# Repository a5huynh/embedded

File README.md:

embedded projects
=================

Source for various embedded projects that I've completed or in progress.

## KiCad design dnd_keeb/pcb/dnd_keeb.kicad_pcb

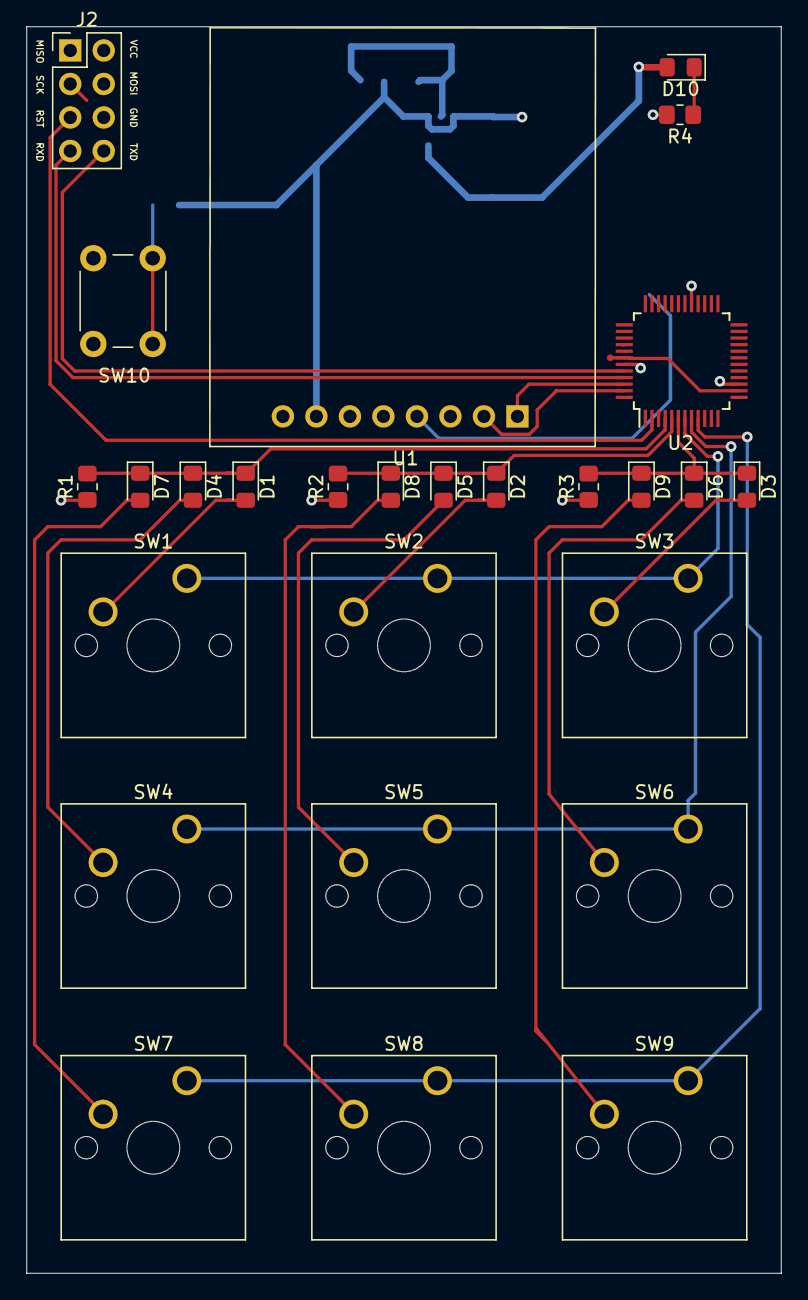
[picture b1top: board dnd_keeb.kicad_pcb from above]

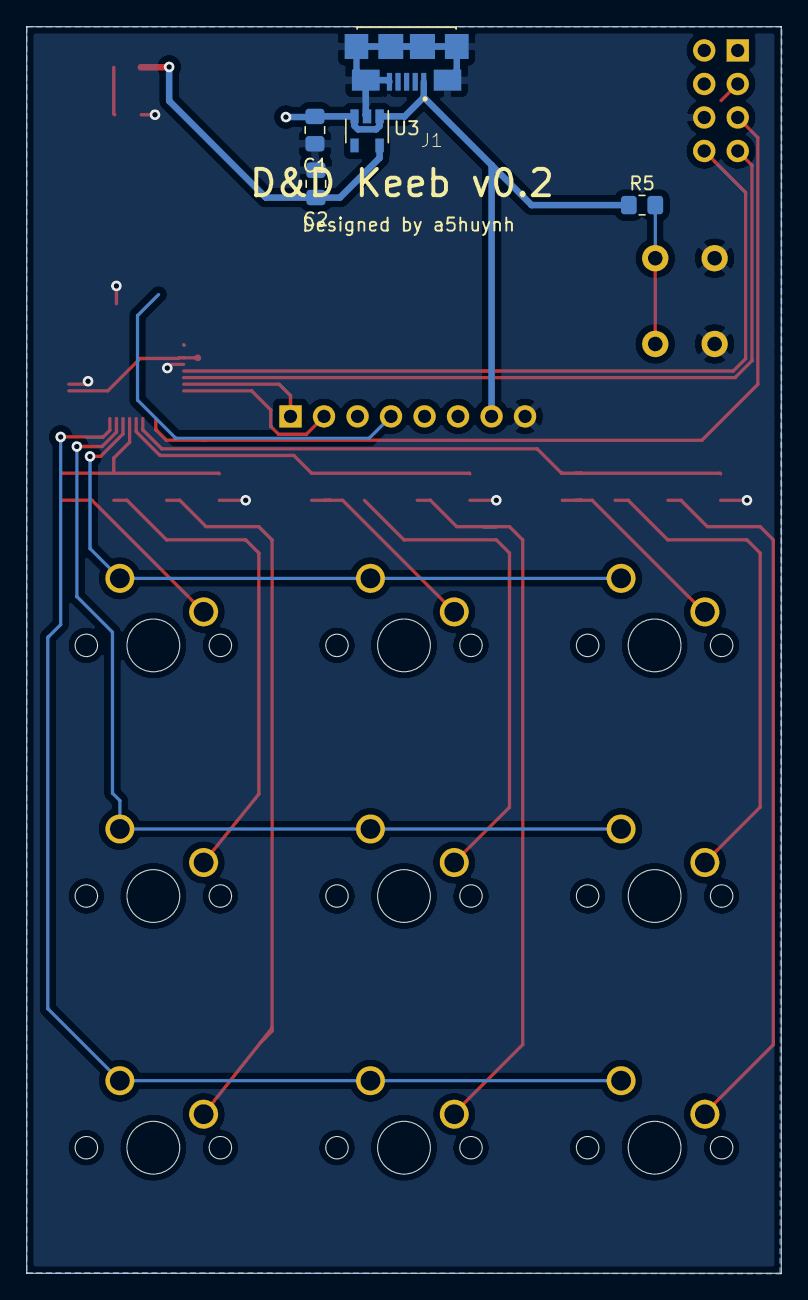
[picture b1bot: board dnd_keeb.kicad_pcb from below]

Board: 2 copper layers, 57.2 x 94.5 mm, 32 parts (5 on the bottom side), 28 nets.

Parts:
C1, C2: 1uF; C_0805_2012Metric_Pad1.18x1.45mm_HandSolder
D1, D2, D3, D4, D5, D6, D7, D8, D9: D; D_0805_2012Metric_Pad1.15x1.40mm_HandSolder
D10: PWR; LED_0805_2012Metric_Pad1.15x1.40mm_HandSolder
J1: USB-B Micro Receptacle 10118192-0002LF; AMPHENOL_10118192-0002LF
J2: Conn_02x04_Odd_Even; PinHeader_2x04_P2.54mm_Vertical
R1, R2, R3: 10k; R_0805_2012Metric_Pad1.20x1.40mm_HandSolder
R4, R5: 330; R_0805_2012Metric_Pad1.20x1.40mm_HandSolder
SW1, SW2, SW3, SW4, SW5, SW6, SW7, SW8, SW9: SW_DIP_x01; SW_Cherry_MX_1.00u_PCB
SW10: SW_Push; SW_PUSH_6mm
U1: OLED_326; Adafruit_326
U2: ATmega4809-A; TQFP-48_7x7mm_P0.5mm
U3: AP7343-33W5-7; SOT-23-5

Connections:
3v3: C2.1, D10.2, U3.5
/RXD: J2.7, U2.45
/TXD: J2.8, U2.44
COL1: SW1.1, SW2.1, SW3.1, U2.7
COL2: SW4.1, SW5.1, SW6.1, U2.8
COL3: SW7.1, SW8.1, SW9.1, U2.9
GND: C1.2, C2.2, J1.5, J1.S1, J1.S2, J1.S3, J1.S4, J1.S5, J1.S6, J2.6, R1.1, R2.1, R3.1, R4.2, SW10.1, U1.8, U2.15, U2.29, U2.43, U3.2
MISO: J2.3, U2.1
MOSI: J2.1, U2.48
unnamed: D1.2, SW1.2
unnamed: D2.2, SW2.2
unnamed: D3.2, SW3.2
unnamed: D4.2, SW4.2
unnamed: D5.2, SW5.2
unnamed: D6.2, SW6.2
unnamed: D7.2, SW7.2
unnamed: D8.2, SW8.2
unnamed: D9.2, SW9.2
unnamed: D10.1, R4.1
unnamed: R5.2, SW10.2, U2.40
ROW1: D1.1, D4.1, D7.1, R1.2, U2.4
ROW2: D2.1, D5.1, D8.1, R2.2, U2.5
ROW3: D3.1, D6.1, D9.1, R3.2, U2.6
SCK: J2.5, U2.2
SCL: U1.2, U2.47
SDA: U1.1, U2.46
UPDI: J2.4, U2.41
VCC: C1.1, J1.1, J2.2, R5.1, U1.7, U2.14, U2.42, U3.1, U3.3

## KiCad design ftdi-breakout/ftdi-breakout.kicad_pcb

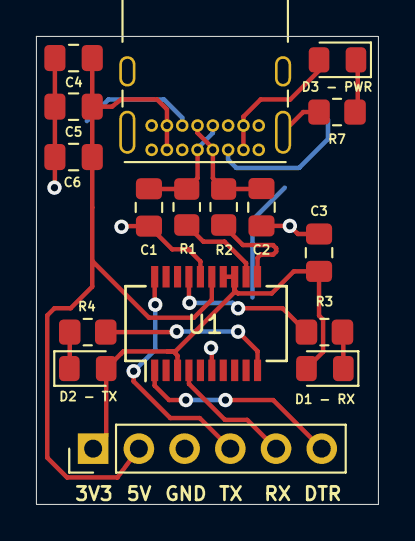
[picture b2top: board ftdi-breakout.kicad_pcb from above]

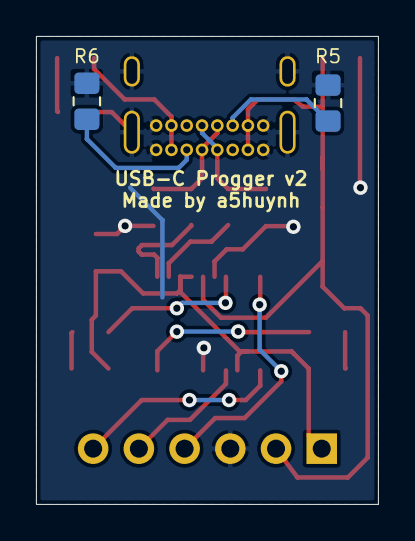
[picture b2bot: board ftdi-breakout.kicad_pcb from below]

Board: 2 copper layers, 19.0 x 26.0 mm, 19 parts (2 on the bottom side), 17 nets.

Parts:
C1, C2, C6: 47pF; C_0805_2012Metric_Pad1.18x1.45mm_HandSolder
C3, C5: 100nF; C_0805_2012Metric_Pad1.18x1.45mm_HandSolder
C4: 10nF; C_0805_2012Metric_Pad1.18x1.45mm_HandSolder
D1 - RX, D3 - PWR: RX Red; LED_0805_2012Metric_Pad1.15x1.40mm_HandSolder
D2 - TX: TX Green; LED_0805_2012Metric_Pad1.15x1.40mm_HandSolder
J1: Conn_01x06; PinHeader_1x06_P2.54mm_Vertical
J2: USB_C_Receptacle_USB2.0; USB_C_Receptacle_GCT_USB4085
R1, R2: 27; R_0805_2012Metric_Pad1.20x1.40mm_HandSolder
R3, R4, R7: 270; R_0805_2012Metric_Pad1.20x1.40mm_HandSolder
R5, R6: 5.1K; R_0805_2012Metric_Pad1.20x1.40mm_HandSolder
U1: FT231XS; SSOP-20_3.9x8.7mm_P0.635mm

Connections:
/3V3OUT: C3.2, D1 - RX.2, D2 - TX.2, J1.1, U1.3, U1.13, U1.14
/CBUS1: R3.1, U1.17
/CBUS2: R4.1, U1.10
/D+: C2.2, J2.A6, J2.B6, R2.2
/D-: C1.1, J2.A7, J2.B7, R1.2
/DTR: J1.6, U1.1
/RX: J1.5, U1.4
/TX: J1.4, U1.20
/VBUS: C4.2, C5.1, C6.1, D3 - PWR.2, J1.2, J2.A4, J2.A9, J2.B4, J2.B9, U1.15
GND: C1.2, C2.1, C3.1, C4.1, C5.2, C6.2, J1.3, J2.A1, J2.A12, J2.B1, J2.B12, J2.S1, R5.2, R6.2, R7.1, U1.6, U1.16
unnamed: D1 - RX.1, R3.2
unnamed: D2 - TX.1, R4.2
unnamed: D3 - PWR.1, R7.2
unnamed: J2.A5, R6.1
unnamed: J2.B5, R5.1
unnamed: R1.1, U1.12
unnamed: R2.1, U1.11

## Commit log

2020-07-15 ✨ Add esp32-display project
2020-07-15 ✨ [esp32-display] Add blank constants.cpp
2020-07-28 📝 Adding a basic readme file
2020-07-28 ✨ [dnd_keeb] Initial commit, basic switch matrix functionality
2020-08-01 ✨ [dnd_keeb] Add OLED support
    - Add SSD1306 & GFX library dependencies.
    - Read keyboard state in a separate function & handle dice roll.
    - Move kb debug printout to display.
2020-09-10 ✨ [dnd_keeb] Add key cap STL files
2020-09-10 ♻️ [dnd_keeb] Update row/col pins to match schematic
2020-09-30 ✨ [dnd_keeb] Moving constants and add ability to toggle thru different screens.
2020-09-30 📝 [logo_lights] Add docs for ESP-01 & WS2812B
2020-11-17 ✨ [logo_lights] WiFi connectivity and basic blinky modes
2020-11-18 ✨ [logo_lights] state indicators & modes update
    * booting/error state indications only use a single LED
    * single color modes turn off disco / blinking
2021-04-01 ✨ [ftdi-breakout] Add KiCAD files for USB-C FT231X breakout
2021-04-01 📄 [ftdi-breakout] Adding datasheet for FT231X IC used
2021-04-01 [ftdi-breakout] Add version number to PCB
2021-04-09 🐛 [ftdi-breakout] Add missing resistors for CC1/CC2 USB-C connector and attach TX/RX LEDs to 3v3out
2021-04-12 🏗 [ftdi-breakout] Revision 2
2021-04-12 📝 [dnd_keeb] Add gitignore for PCB folder
2021-04-12 🧹 [dnd_keeb] ERC check & cleanup
2021-04-12 🏗 [dnd_keeb] Add KiCAD files for dnd_keeb. Version 0.1 sent off for manufacturing
2021-04-12 ✨ [dnd_keeb] Update deps & add rot constant
2021-04-12 🐛 [dnd_keeb] Fix pinout for OLED & update footprints + pcb
2021-05-16 ✨ [dnd_keeb] v0.2
    - Added atmega4809 to board, routed row/cols + lcd to mcu
    - Added ICSP + TX/RX pinout to program / debug
    - Added USB micro for power
2021-05-17 🐛 [dnd_keeb] AP2112K-3.3 not available, switching to AP7343-33W5
2021-05-19 Add `fp-info-cache` to gitignore
2021-09-16 🐛 Updating schematic so that UPDI is correctly broken out to a PIN
